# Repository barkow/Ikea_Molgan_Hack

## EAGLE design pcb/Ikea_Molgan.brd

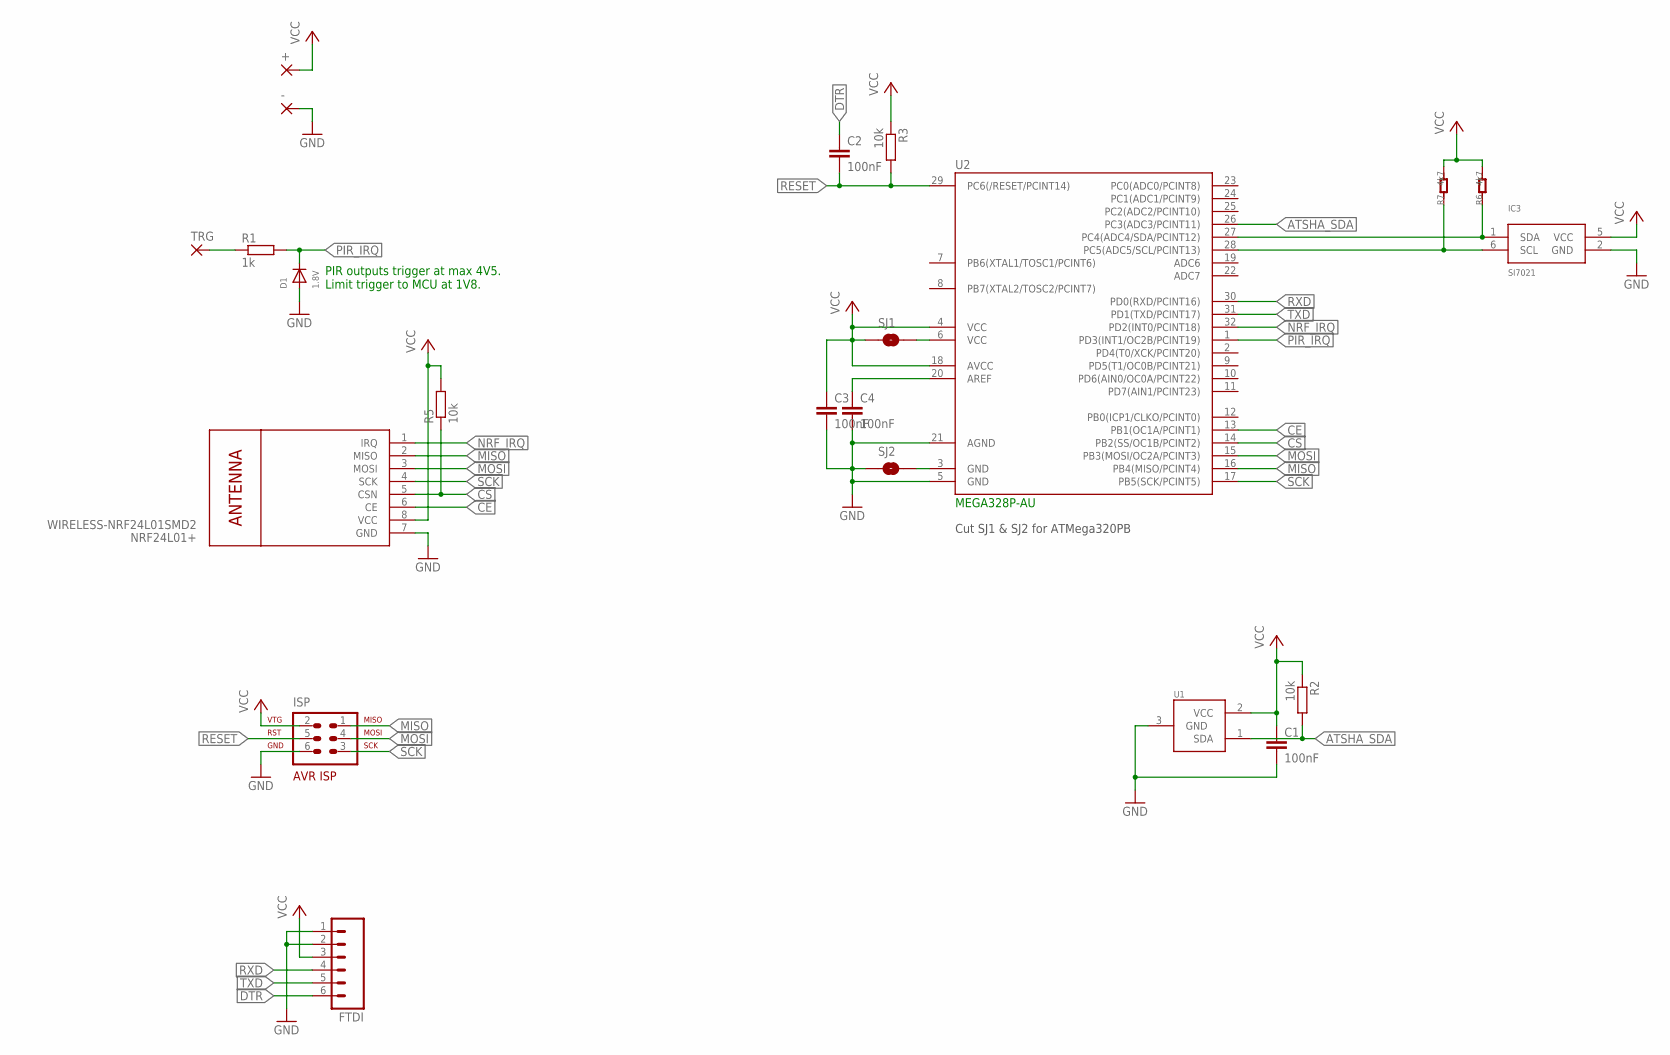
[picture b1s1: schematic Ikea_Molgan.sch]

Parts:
+: WIREPADSMD2,54-5,08; SMD2,54-5,08
-: WIREPADSMD2,54-5,08; SMD2,54-5,08
C1, C2, C3, C4: 100nF; C0805
D1: 1.8V; SOD-123
FTDI: M06SIP; 1X06
IC3: SI7021; DFN6
ISP: AVR-ISP-6
NRF24L01+: WIRELESS-NRF24L01SMD2; WIRELESS-NRF24L01-SMD-2
R1: 1k; R0805
R2, R3, R5: 10k; R0805
R6, R7: 4k7; R0402
SJ1, SJ2: SOLDERJUMPERTRACE; SJ_2S-TRACE
TRG: WIREPADSMD2,54-5,08; SMD2,54-5,08
U1: IC_ATSHA204A_CRYPT; SOT23-3
U2: MEGA328P-AU; TQFP32-08

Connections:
ATSHA_SDA: R2.2, U1.1 (SDA), U2.26 (PC3(ADC3/PCINT11))
CE: NRF24L01+.6 (CE), U2.13 (PB1(OC1A/PCINT1))
CS: NRF24L01+.5 (CSN), R5.1, U2.14 (PB2(SS/OC1B/PCINT2))
DTR: C2.1, FTDI.6
GND: -.1, C1.2, C3.2, C4.2, D1.A, FTDI.1, FTDI.2, IC3.2 (GND), ISP.6, NRF24L01+.7 (GND), SJ2.1, U1.3 (GND), U2.5 (GND), U2.21 (AGND)
MISO: ISP.1, NRF24L01+.2 (MISO), U2.16 (PB4(MISO/PCINT4))
MOSI: ISP.4, NRF24L01+.3 (MOSI), U2.15 (PB3(MOSI/OC2A/PCINT3))
unnamed: R1.1, TRG.1
unnamed: SJ1.2, U2.6 (VCC)
unnamed: SJ2.2, U2.3 (GND)
unnamed: C4.1, U2.20 (AREF)
NRF_IRQ: NRF24L01+.1 (IRQ), U2.32 (PD2(INT0/PCINT18))
PIR_IRQ: D1.C, R1.2, U2.1 (PD3(INT1/OC2B/PCINT19))
RESET: C2.2, ISP.5, R3.2, U2.29 (PC6(/RESET/PCINT14))
RXD: FTDI.4, U2.30 (PD0(RXD/PCINT16))
SCK: ISP.3, NRF24L01+.4 (SCK), U2.17 (PB5(SCK/PCINT5))
SCL: IC3.6 (SCL), R7.1, U2.28 (PC5(ADC5/SCL/PCINT13))
SDA: IC3.1 (SDA), R6.1, U2.27 (PC4(ADC4/SDA/PCINT12))
TXD: FTDI.5, U2.31 (PD1(TXD/PCINT17))
VCC: +.1, C1.1, C3.1, FTDI.3, IC3.5 (VCC), ISP.2, NRF24L01+.8 (VCC), R2.1, R3.1, R5.2, R6.2, R7.2, SJ1.1, U1.2 (VCC), U2.4 (VCC), U2.18 (AVCC)

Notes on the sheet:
PIR outputs trigger at max 4V5. Limit trigger to MCU at 1V8.
Cut SJ1 & SJ2 for ATMega320PB

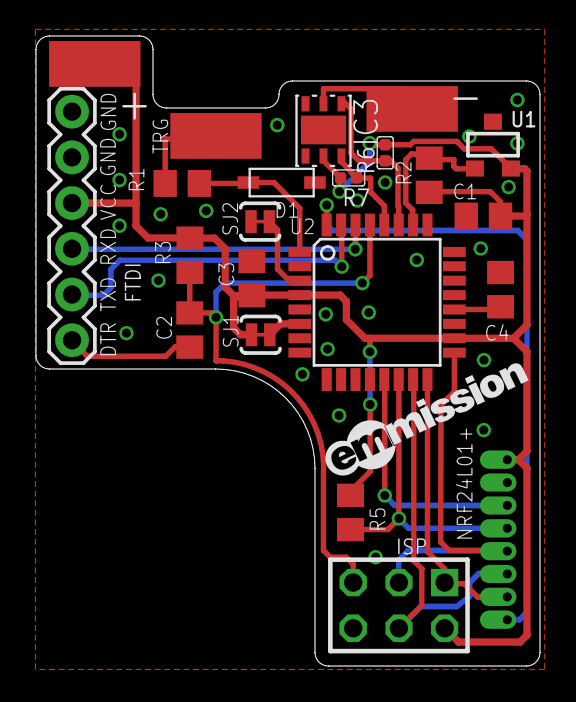
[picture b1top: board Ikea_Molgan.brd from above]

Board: 2 copper layers, 28.0 x 35.0 mm, 23 parts (0 on the bottom side), 20 nets.

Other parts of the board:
U$1: EMMISSION_LOGO_12MM_NOTAG

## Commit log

2017-08-27 Temperatursensor hinzugefügt und LED entfernt

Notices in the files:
parts and their libraries:
SparkFun: Licensing: CC v3.0 Share-Alike You are welcome to use this library for commercial purposes.
